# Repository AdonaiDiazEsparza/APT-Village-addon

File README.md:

# APT-Villa-addon
Repositorio de los recursos del Addon para el APT Village. Este es un pequeño recuerdo que se les da a las personas que participen en alguno de nuestras platicas.

## Hardware

- La iluminación consta de 11 Leds (6 de color rojo, 2 de color blanco y 3 traseros de color rojo).
- El chip progragramable es un CH32v003F4P6

## Firmware

### Programación

Para poder programar el chip es necesario utilizar un programador especializado, nosotros recomendamos el programador de WCH-link, pero puede funcionar otro programador que tenga soporte para chips CH32 o para arquitectura RISC-V

### Compilación

Para compilar el firmware del chip usa el comando ```make build``` para generar los archivos ```.bin``` y ```.hex```. 
Es necesario instalar los paquetes necesarios:

```shell
apt-get install build-essential libnewlib-dev gcc-riscv64-unknown-elf libusb-1.0-0-dev libudev-dev gdb-multiarch
```
Si deseas programar el chip utiliza el comando ```make flash```. 
Mas información al respecto del desarrollo de firmware con chips CH32vX, puedes ver los ejemplos en el repositorio de [CH32FUN](https://github.com/cnlohr/ch32fun).

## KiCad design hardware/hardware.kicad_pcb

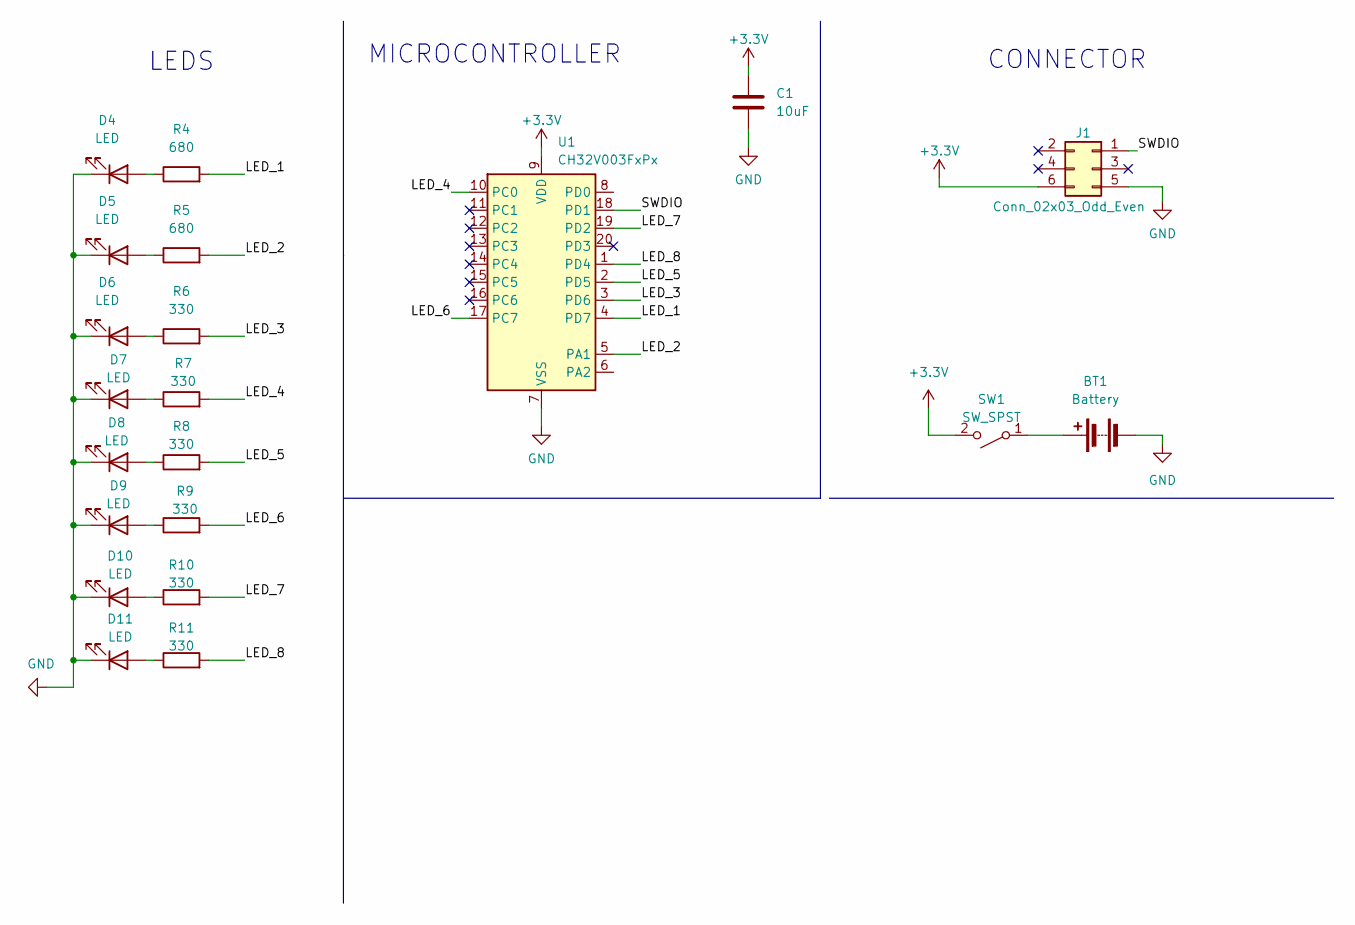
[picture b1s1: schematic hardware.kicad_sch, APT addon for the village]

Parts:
BT1: Battery; BAT-HLD-001; LCSC# C964833
C1: 10uF; C_0603_1608Metric; LCSC# C5137483
D4, D5: LED; LED_0402_1005Metric; LCSC# C917191
D6, D7, D8, D9, D10, D11: LED; LED_0402_1005Metric; LCSC# C779449
J1: Conn_02x03_Odd_Even; PinHeader_2x03_P2.54mm_Vertical_SMD; LCSC# C3294461
R4, R5: 680; R_0402_1005Metric_Pad0.72x0.64mm_HandSolder; LCSC# C137948
R6, R7, R8, R9, R10, R11: 330; R_0402_1005Metric_Pad0.72x0.64mm_HandSolder; LCSC# C49653054
SW1: SW_SPST; SW_SPDT_PCM12; LCSC# C431540
U1: CH32V003FxPx; TSSOP-20_4.4x6.5mm_P0.65mm; LCSC# C5187096

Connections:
+3.3V: C1.1, J1.6, SW1.2 (B), U1.9 (VDD)
/LED_1: R4.2, U1.4 (PD7)
/LED_2: R5.2, U1.5 (PA1)
/LED_3: R6.2, U1.3 (PD6)
/LED_4: R7.2, U1.10 (PC0)
/LED_5: R8.2, U1.2 (PD5)
/LED_6: R9.2, U1.17 (PC7)
/LED_7: R10.2, U1.19 (PD2)
/LED_8: R11.2, U1.1 (PD4)
/SWDIO: J1.1, U1.18 (PD1)
GND: BT1.1 (-), C1.2, D4.1 (K), D5.1 (K), D6.1 (K), D7.1 (K), D8.1 (K), D9.1 (K), D10.1 (K), D11.1 (K), J1.5, U1.7 (VSS)
unnamed: BT1.2 (+), SW1.1 (A)
unnamed: D4.2 (A), R4.1
unnamed: D5.2 (A), R5.1
unnamed: D6.2 (A), R6.1
unnamed: D7.2 (A), R7.1
unnamed: D8.2 (A), R8.1
unnamed: D9.2 (A), R9.1
unnamed: D10.2 (A), R10.1
unnamed: D11.2 (A), R11.1

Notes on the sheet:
LEDS
CONNECTOR
MICROCONTROLLER

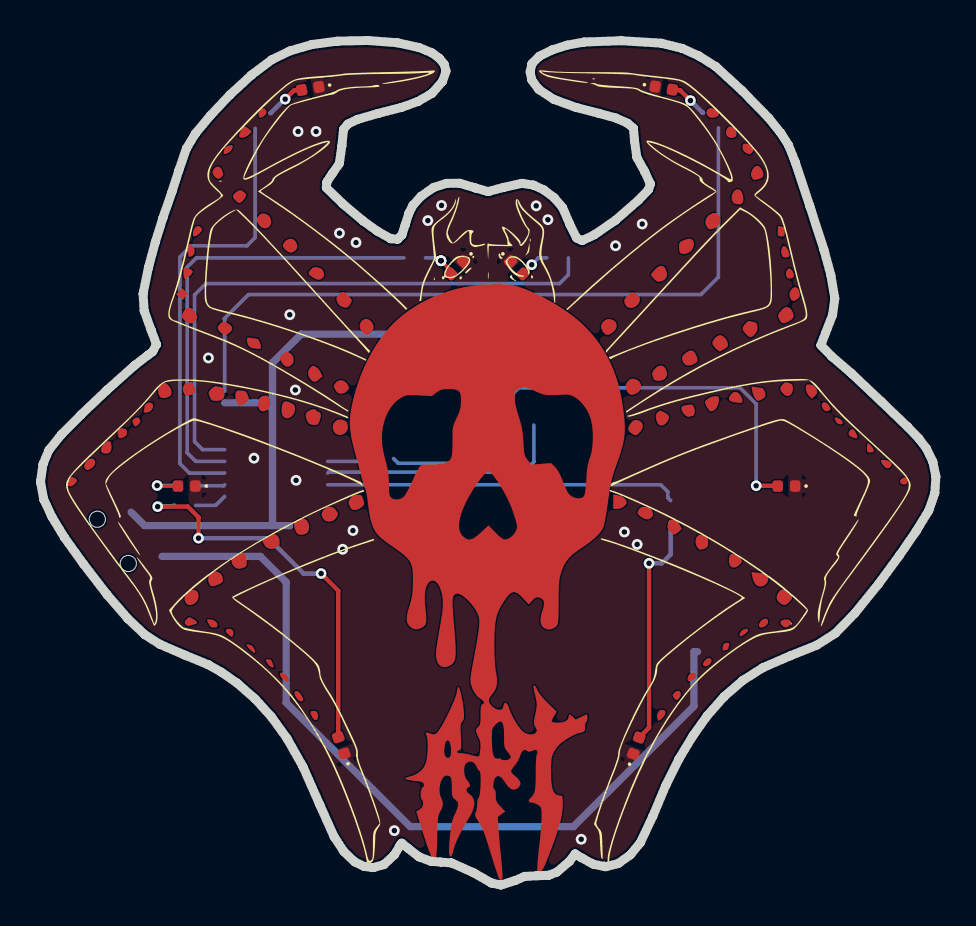
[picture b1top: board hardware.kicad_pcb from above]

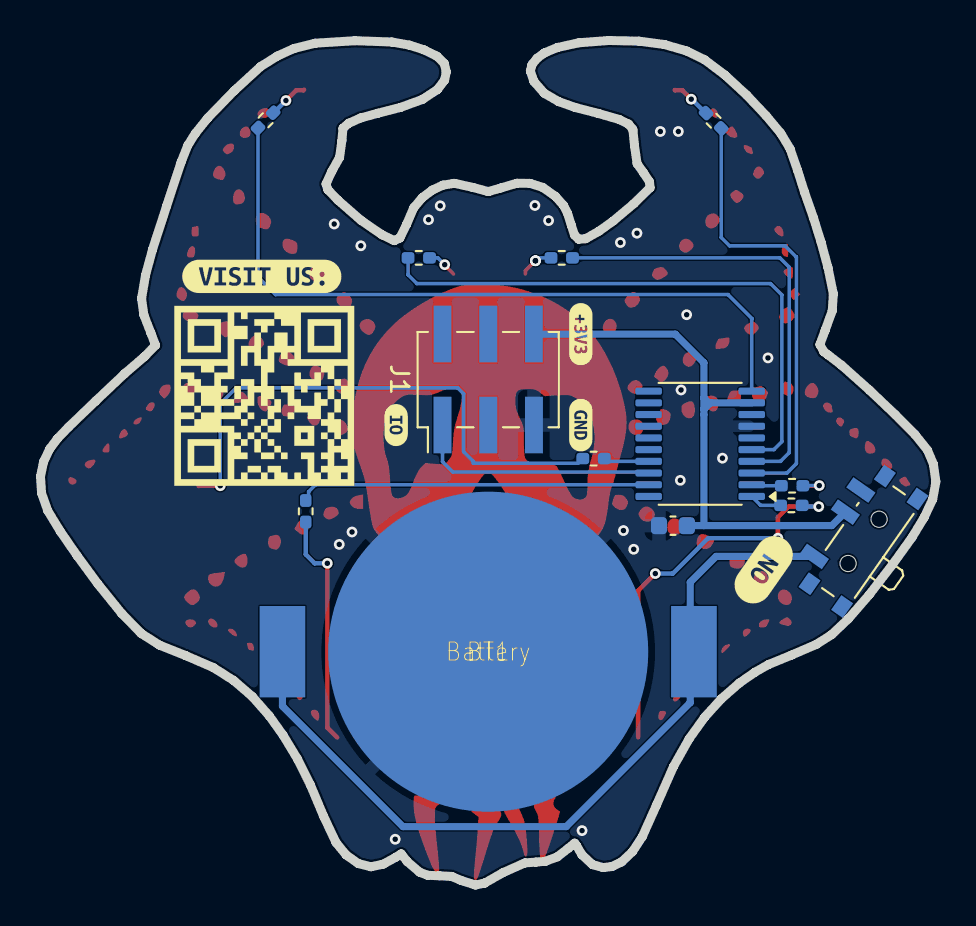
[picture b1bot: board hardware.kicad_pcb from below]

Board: 2 copper layers, 49.7 x 46.9 mm, 26 parts (18 on the bottom side), 20 nets.

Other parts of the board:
kibuzzard-6AD7C383: G***; kibuzzard-6AD7C383
kibuzzard-6986EF7D: G***; kibuzzard-6986EF7D
kibuzzard-6986EFAB: G***; kibuzzard-6986EFAB
kibuzzard-6986EFC1: G***; kibuzzard-6986EFC1
kibuzzard-6986EFDC: G***; kibuzzard-6986EFDC

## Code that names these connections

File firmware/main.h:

#include "ch32fun.h"
#include <stdbool.h>
#include <stdio.h>

#define RIGHT_EYE   PA1
#define LEFT_EYE    PD0
#define NOSE        PA2

#define LED_1       PD4
#define LED_2       PD5
#define LED_3       PD2
#define LED_4       PD3
#define LED_5       PC0
#define LED_6       PD6
#define LED_7       PC1
#define LED_8       PC2

// Init leds
#define INIT_LED(led) funPinMode(led, GPIO_Speed_10MHz | GPIO_CNF_OUT_PP);

// Struct to control the pwm led
typedef struct {
    uint8_t led;
    volatile uint16_t pwm;
} led_t;

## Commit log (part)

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2026-01-29 feat(hw): add hardware project
2026-02-01 feat: add resources
2026-02-01 feat: add zones with no cooper
2026-02-02 feat: add footprints
2026-02-04 feat: update pcb
2026-02-04 feat: add routes
2026-02-05 feat: add vias
2026-02-05 feat: add more designs
2026-02-06 feat: add zones for designs
2026-02-06 refactor(hw): remove routes
2026-02-06 feat(fw): add files for firmware
2026-02-07 feat(hw): add qr and components number
2026-02-23 test: timer on firmware
2026-02-25 feat: add struct for the pwm
2026-02-26 feat: add pwm examples
2026-02-26 feat: add delay function
2026-03-04 feat: add a sequence
2026-03-04 feat: add more sequences
2026-03-04 feat: add sequence for addon
2026-03-04 feat: delete unnecessary code
2026-03-04 feat: add documentation
2026-03-04 fix: update number
2026-03-04 feat: update readme
2026-03-04 feat: modify the display of the images
    Updated image alignment and sizes in README.
2026-03-04 feat: update titles
    Added details about hardware and firmware programming.
2026-03-04 fix: title of hardware
